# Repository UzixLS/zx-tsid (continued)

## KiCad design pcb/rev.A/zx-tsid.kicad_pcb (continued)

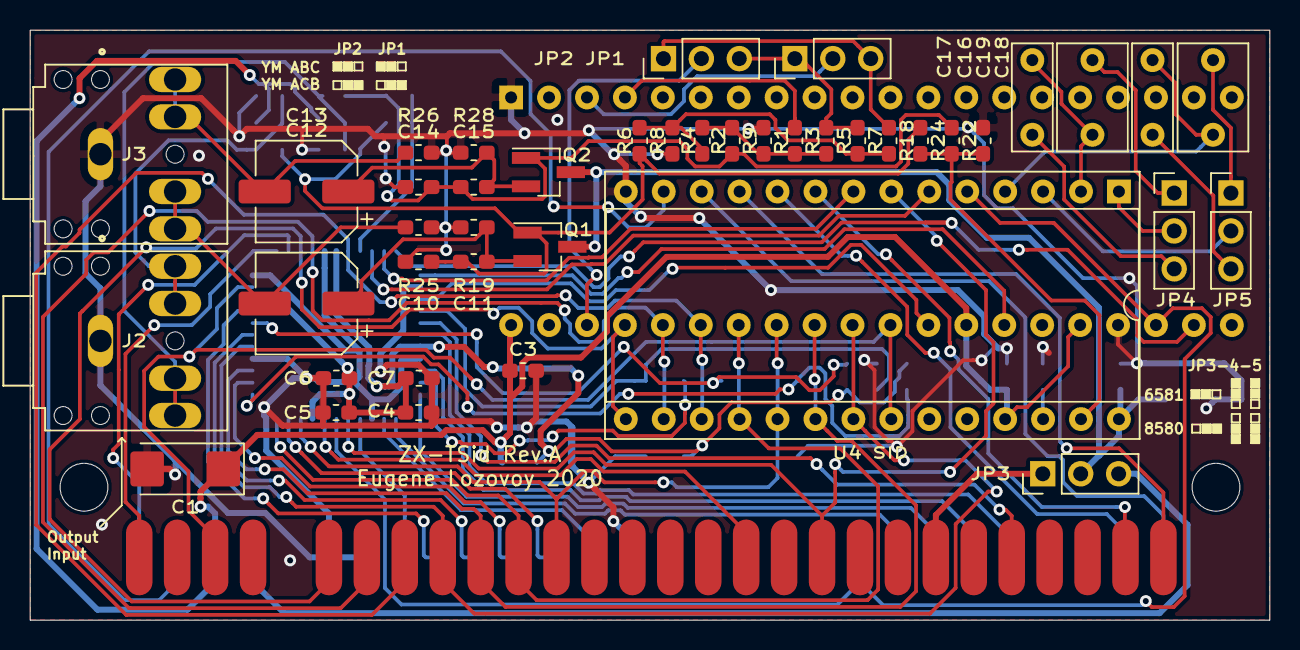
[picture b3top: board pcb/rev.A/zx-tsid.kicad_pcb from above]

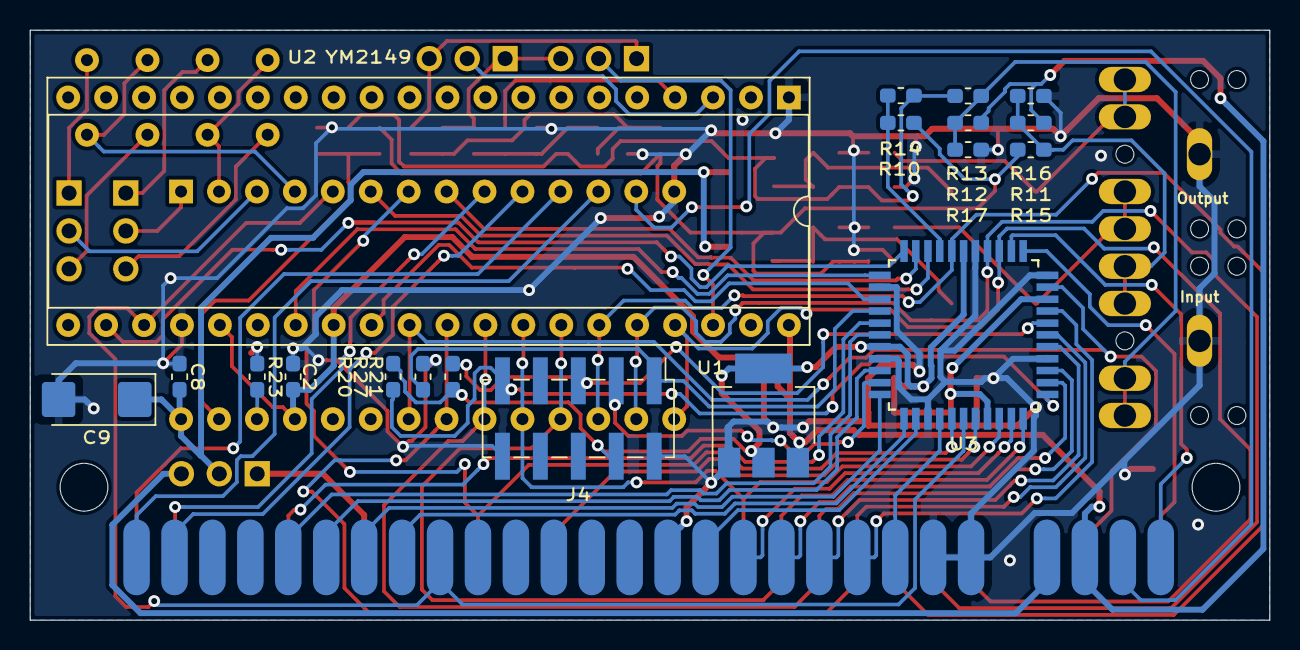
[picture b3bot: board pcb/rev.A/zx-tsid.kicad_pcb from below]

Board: 2 copper layers, 83.0 x 39.5 mm, 64 parts (19 on the bottom side), 70 nets.

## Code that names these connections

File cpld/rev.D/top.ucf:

#PACE: Start of Constraints generated by PACE
#PACE: Start of PACE I/O Pin Assignments
NET "a<0>"  LOC = "p40"  ;
NET "a<10>"  LOC = "p61"  ;
NET "a<11>"  LOC = "p60"  ;
NET "a<12>"  LOC = "p33"  ;
NET "a<14>"  LOC = "p31"  ;
NET "a<15>"  LOC = "p32"  ;
NET "a<1>"  LOC = "p42"  ;
NET "a<2>"  LOC = "p43"  ;
NET "a<3>"  LOC = "p51"  ;
NET "a<4>"  LOC = "p39"  ;
NET "a<5>"  LOC = "p35"  ;
NET "a<6>"  LOC = "p36"  ;
NET "a<7>"  LOC = "p34"  ;
NET "a<8>"  LOC = "p57"  ;
NET "a<9>"  LOC = "p59"  ;
NET "cfg"  LOC = "p27"  ;
NET "clk32"  LOC = "p17"  ;
NET "clkcpu"  LOC = "p15"  ;
NET "d<0>"  LOC = "p44"  ;
NET "d<1>"  LOC = "p45"  ;
NET "d<2>"  LOC = "p46"  ;
NET "d<3>"  LOC = "p49"  ;
NET "d<4>"  LOC = "p58"  ;
NET "d<5>"  LOC = "p48"  ;
NET "d<6>"  LOC = "p47"  ;
NET "d<7>"  LOC = "p38"  ;
NET "n_iorq"  LOC = "p50"  ;
NET "n_iorqge"  LOC = "p52"  ;
NET "n_rd"  LOC = "p63"  ;
NET "n_wait" LOC = "p56" ;
NET "n_wr"  LOC = "p62"  ;
NET "rst_n"  LOC = "p64"  ;
NET "sid_a<0>"  LOC = "p8"  ;
NET "sid_a<1>"  LOC = "p7"  ;
NET "sid_a<2>"  LOC = "p4"  ;
NET "sid_a<3>"  LOC = "p5"  ;
NET "sid_a<4>"  LOC = "p2"  ;
NET "sid_clk"  LOC = "p1"  ;
NET "sid_cs"  LOC = "p6"  ;
NET "sid_d<0>"  LOC = "p16"  ;
NET "sid_d<1>"  LOC = "p9"  ;
NET "sid_d<2>"  LOC = "p12"  ;
NET "sid_d<3>"  LOC = "p19"  ;
NET "sid_d<4>"  LOC = "p18"  ;
NET "sid_d<5>"  LOC = "p20"  ;
NET "sid_d<6>"  LOC = "p10"  ;
NET "sid_d<7>"  LOC = "p11"  ;
NET "sid_rst"  LOC = "p23"  ;
NET "sid_wr"  LOC = "p13"  ;

#PACE: Start of PACE Area Constraints
#PACE: Start of PACE Prohibit Constraints
#PACE: End of Constraints generated by PACE
#Created by Constraints Editor (xc9572xl-vq64-10) - 2020/12/09
NET "clk32" TNM_NET = clk32;
TIMESPEC TS_clk32 = PERIOD "clk32" 32 MHz HIGH 50%;
NET "clkcpu" TNM_NET = clkcpu;
TIMESPEC TS_clkcpu = PERIOD "clkcpu" 7 MHz HIGH 50%;

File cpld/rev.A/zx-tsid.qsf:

# -------------------------------------------------------------------------- #
#
# Copyright (C) 1991-2013 Altera Corporation
# Your use of Altera Corporation's design tools, logic functions 
# and other software and tools, and its AMPP partner logic 
# functions, and any output files from any of the foregoing 
# (including device programming or simulation files), and any 
# associated documentation or information are expressly subject 
# to the terms and conditions of the Altera Program License 
# Subscription Agreement, Altera MegaCore Function License 
# Agreement, or other applicable license agreement, including, 
# without limitation, that your use is for the sole purpose of 
# programming logic devices manufactured by Altera and sold by 
# Altera or its authorized distributors.  Please refer to the 
# applicable agreement for further details.
#
# -------------------------------------------------------------------------- #
#
# Quartus II 64-Bit
# Version 13.0.1 Build 232 06/12/2013 Service Pack 1 SJ Full Version
# Date created = 13:37:37  May 16, 2020
#
# -------------------------------------------------------------------------- #
#
# Notes:
#
# 1) The default values for assignments are stored in the file:
#		zx-tsid_assignment_defaults.qdf
#    If this file doesn't exist, see file:
#		assignment_defaults.qdf
#
# 2) Altera recommends that you do not modify this file. This
#    file is updated automatically by the Quartus II software
#    and any changes you make may be lost or overwritten.
#
# -------------------------------------------------------------------------- #


set_global_assignment -name FAMILY MAX3000A
set_global_assignment -name DEVICE "EPM3064ATC44-10"
set_global_assignment -name TOP_LEVEL_ENTITY top
set_global_assignment -name ORIGINAL_QUARTUS_VERSION "13.0 SP1"
set_global_assignment -name PROJECT_CREATION_TIME_DATE "13:37:37  MAY 16, 2020"
set_global_assignment -name LAST_QUARTUS_VERSION "13.0 SP1"
set_global_assignment -name PROJECT_OUTPUT_DIRECTORY output_files
set_global_assignment -name DEVICE_FILTER_PIN_COUNT 44
set_global_assignment -name ERROR_CHECK_FREQUENCY_DIVISOR "-1"
set_global_assignment -name MIN_CORE_JUNCTION_TEMP 0
set_global_assignment -name MAX_CORE_JUNCTION_TEMP 85
set_global_assignment -name SDC_FILE clocks.sdc
set_global_assignment -name VERILOG_FILE top.v
set_global_assignment -name VHDL_INPUT_VERSION VHDL_2008
set_global_assignment -name VHDL_SHOW_LMF_MAPPING_MESSAGES OFF
set_global_assignment -name VERILOG_INPUT_VERSION SYSTEMVERILOG_2005
set_global_assignment -name VERILOG_SHOW_LMF_MAPPING_MESSAGES OFF
set_global_assignment -name MAX7000_DEVICE_IO_STANDARD "3.3-V LVTTL"
set_location_assignment PIN_8 -to a[0]
set_location_assignment PIN_10 -to d[7]
set_location_assignment PIN_12 -to a15
set_location_assignment PIN_13 -to a14
set_location_assignment PIN_14 -to d[0]
set_location_assignment PIN_15 -to d[1]
set_location_assignment PIN_18 -to d[2]
set_location_assignment PIN_19 -to dac
set_location_assignment PIN_20 -to sid_clk
set_location_assignment PIN_21 -to sid_cs
set_location_assignment PIN_22 -to ay_clk
set_location_assignment PIN_37 -to clk
set_location_assignment PIN_23 -to ay_bdir
set_location_assignment PIN_25 -to ay_bc1
set_location_assignment PIN_27 -to n_m1
set_location_assignment PIN_28 -to a[4]
set_location_assignment PIN_31 -to a[5]
set_location_assignment PIN_33 -to a[6]
set_location_assignment PIN_34 -to a[7]
set_location_assignment PIN_35 -to n_iorqge
set_location_assignment PIN_38 -to n_wr
set_location_assignment PIN_40 -to n_iorq
set_location_assignment PIN_2 -to a[2]
set_location_assignment PIN_3 -to d[5]
set_location_assignment PIN_5 -to a[1]
set_location_assignment PIN_6 -to d[6]
set_location_assignment PIN_42 -to d[4]
set_location_assignment PIN_43 -to a[3]
set_location_assignment PIN_44 -to d[3]
set_location_assignment PIN_39 -to n_rst

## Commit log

2020-05-17 initial
2020-06-20 cpld: fix ay
2020-06-20 add delivered files (gerbers, firmware binary, etc) for rev.A
2020-07-22 cpld: fix sid_cs signal
2020-07-29 fix github language detector
2020-10-20 cpld: improve AY port decoding
2020-10-20 pcb: add errata for rev.A
2021-03-16 add pcb rev.B
2021-03-16 add pcb rev.C
2021-03-16 add pcb rev.D
2021-03-16 move cpld firmware for rev.A pcb to dedicated directory
2021-03-16 add cpld firmware for pcb rev.C
2021-04-08 add photos
2021-04-26 fix compatibility with real SID chip (but still isn't tested)
2021-04-26 add cpld firmware for rev.D pcb
2021-05-27 fix pinout for cpld rev.D firmware
2021-07-24 remove cpld rev.C files
2021-07-24 fix compatibility with original ZX Spectrum 48K
2023-09-19 update readme and pcb photo
2026-06-17 remove raw=true from README links
2026-06-17 add atmega firmware
